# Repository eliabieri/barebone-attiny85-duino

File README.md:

# barebone-attiny85-duino
I wanted to create my own little Arduino, so I build one that uses the attiny85.

I designed the PCBs in Eagle and ordered them from oshpark.
My board only needs two passives: one *.1 uF smoothing cap*, a *10K reset resistor* and a *4K7 resistor* for the LED.
The LED is attached to the pin 0 of the attiny, which is also the MOSI pin.

The arduino is programmed via ICSP. You can get a ICSP programmer for under 3 USD on aliexpress.

If you have questions, I`m @eliabieri on twitter.

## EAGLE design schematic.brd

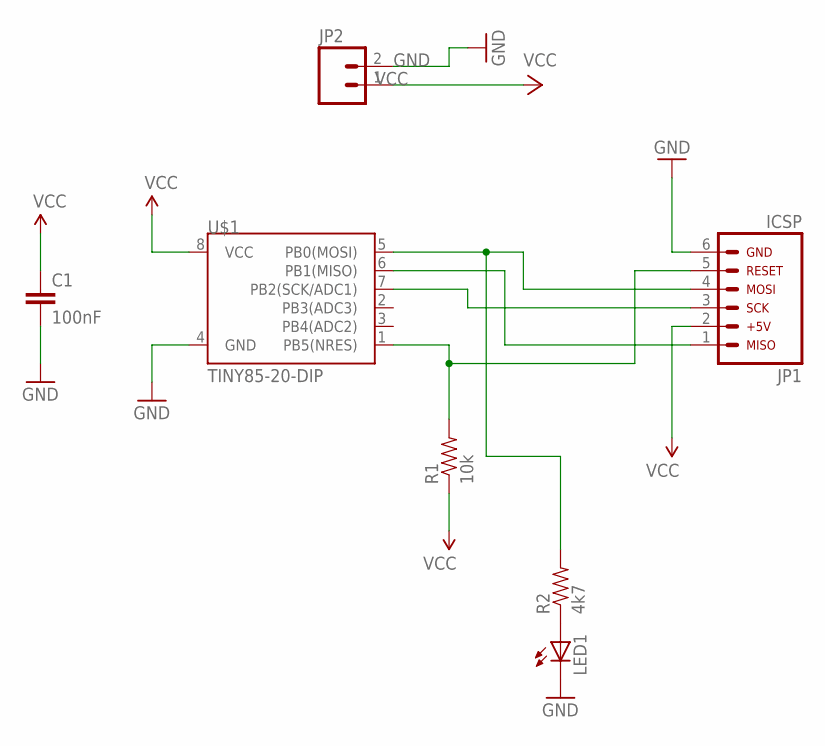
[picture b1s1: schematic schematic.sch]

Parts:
C1: 100nF; CAP-PTH-SMALL-KIT
JP1: ARDUINO_CONN-ICSP; CONN-2X03
JP2: M02LOCK; 1X02_LOCK
LED1: LED5MM
R1: 10k; 1/6W-RES
R2: 4k7; 1/6W-RES
U$1: TINY85-20-DIP; DIP08

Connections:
GND: C1.2, JP1.6, JP2.2, LED1.K (C), U$1.4 (GND)
unnamed: JP1.1, U$1.6 (PB1(MISO))
unnamed: JP1.4, R2.2, U$1.5 (PB0(MOSI))
unnamed: JP1.3, U$1.7 (PB2(SCK/ADC1))
unnamed: JP1.5, R1.2, U$1.1 (PB5(NRES))
unnamed: LED1.A, R2.1
VCC: C1.1, JP1.2, JP2.1, R1.1, U$1.8 (VCC)

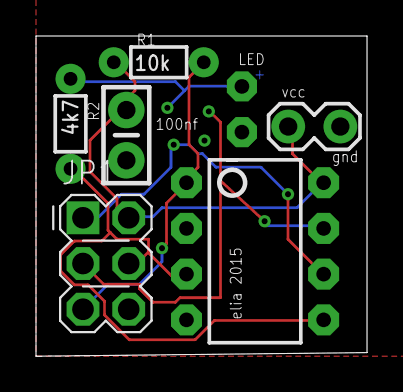
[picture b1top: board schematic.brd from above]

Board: 2 copper layers, 18.4 x 17.8 mm, 7 parts (0 on the bottom side), 7 nets.

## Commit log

2015-07-26 adding eagle files
2015-07-26 created README
2015-07-26 added image

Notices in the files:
parts and their libraries:
SparkFun-Capacitors: Licensing: Creative Commons ShareAlike 4.0 International - https://creativecommons.org/licenses/by-sa/4.0
